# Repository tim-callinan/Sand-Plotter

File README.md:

# Sand-Plotter
This is my stab at building a Sand Plotter. Thank you to Jeff & co over the years. Sorry its taken me this long to upload my files. Ive included the mechanical Solidworks files, KiCAD ECAD files & Arduino code. I found it easier to design my own arduino shield with stepper drivers & arduino code. This machine has been working 8 hours a day, 7days a week probably for the last 4-5 months so I think its pretty reliable.

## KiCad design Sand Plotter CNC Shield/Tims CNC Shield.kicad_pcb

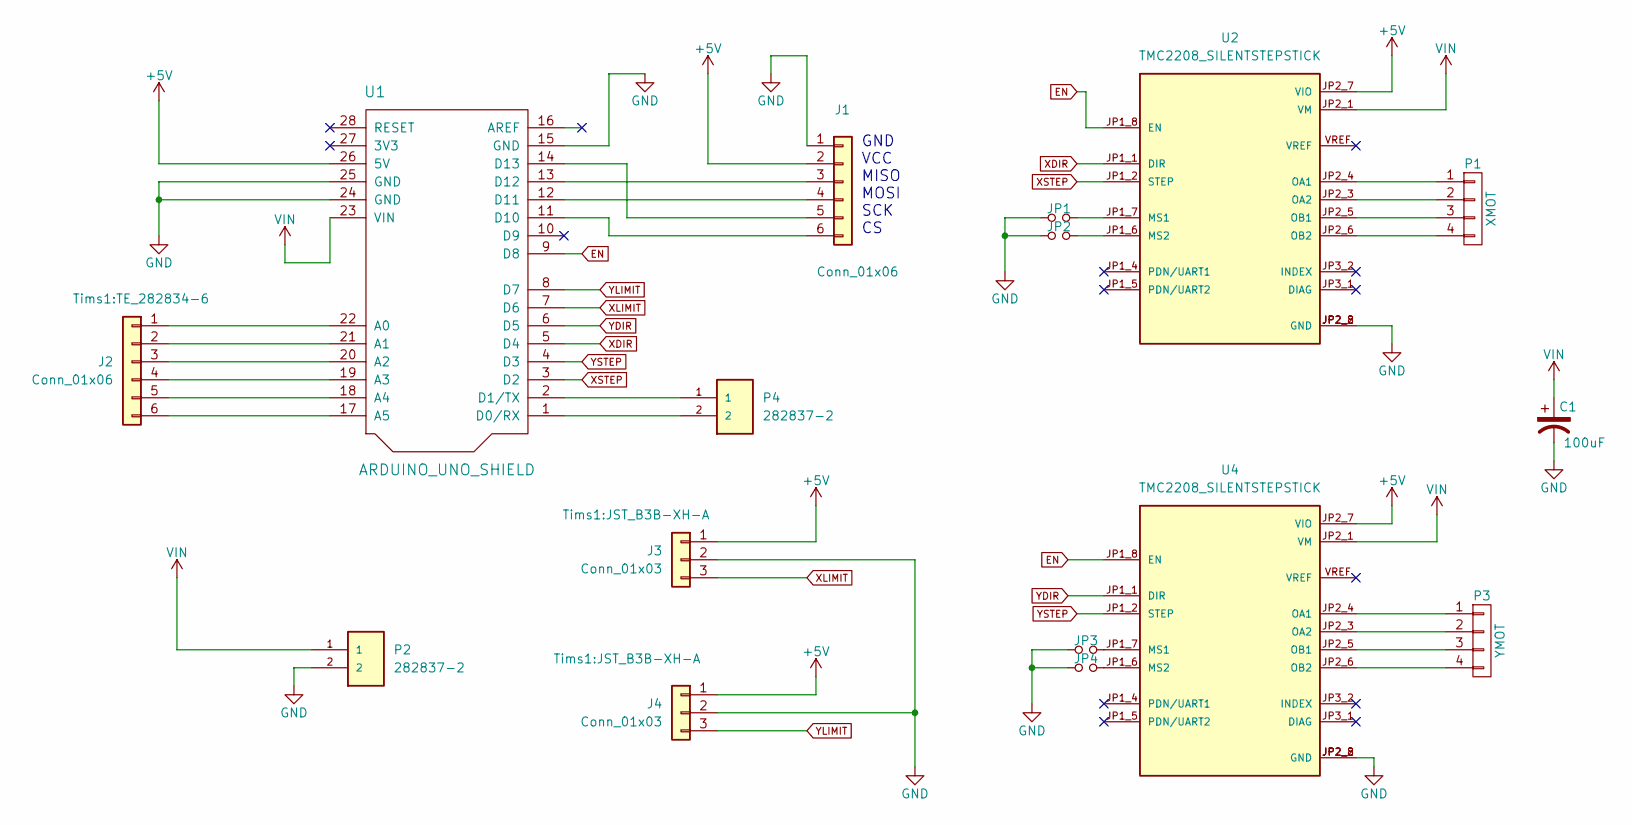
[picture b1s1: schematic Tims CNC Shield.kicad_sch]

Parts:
C1: 100uF; CP_Radial_D8.0mm_P3.50mm
J1: Conn_01x06; PinSocket_1x06_P2.54mm_Horizontal
J2: Conn_01x06; TE_282834-6
J3, J4: Conn_01x03; JST_B3B-XH-A
JP1, JP2, JP3, JP4: Jumper_NO_Small; PinHeader_1x02_P2.54mm_Vertical
P1: XMOT; PinHeader_1x04_P2.54mm_Vertical
P2, P4: 282837-2; TE_282837-2; PARTREV G3
P3: YMOT; PinHeader_1x04_P2.54mm_Vertical
U1: ARDUINO_UNO_SHIELD; ARDUINO_SHIELD
U2, U4: TMC2208_SILENTSTEPSTICK; MODULE_TMC2208_SILENTSTEPSTICK

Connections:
+5V: J1.2, J3.1, J4.1, U1.26 (5V), U2.JP2_7 (VIO), U4.JP2_7 (VIO)
EN: U1.9 (D8), U2.JP1_8 (EN), U4.JP1_8 (EN)
unnamed: J1.3, U1.13 (D12)
unnamed: J1.4, U1.12 (D11)
unnamed: J1.5, U1.14 (D13)
unnamed: J1.6, U1.11 (D10)
unnamed: J2.1, U1.22 (A0)
unnamed: J2.2, U1.21 (A1)
unnamed: J2.3, U1.20 (A2)
unnamed: J2.4, U1.19 (A3)
unnamed: J2.5, U1.18 (A4)
unnamed: P1.1, U2.JP2_4 (OA1)
unnamed: P1.2, U2.JP2_3 (OA2)
unnamed: P1.3, U2.JP2_5 (OB1)
unnamed: P1.4, U2.JP2_6 (OB2)
unnamed: P3.1, U4.JP2_4 (OA1)
unnamed: P3.2, U4.JP2_3 (OA2)
unnamed: P3.3, U4.JP2_5 (OB1)
unnamed: P3.4, U4.JP2_6 (OB2)
unnamed: P4.1, U1.2 (D1/TX)
unnamed: P4.2, U1.1 (D0/RX)
unnamed: JP1.2, U2.JP1_7 (MS1)
unnamed: JP2.2, U2.JP1_6 (MS2)
unnamed: JP3.2, U4.JP1_7 (MS1)
unnamed: JP4.2, U4.JP1_6 (MS2)
VIN: C1.1, P2.1, U1.23 (VIN), U2.JP2_1 (VM), U4.JP2_1 (VM)
XDIR: U1.5 (D4), U2.JP1_1 (DIR)
XLIMIT: J3.3, U1.7 (D6)
XSTEP: U1.3 (D2), U2.JP1_2 (STEP)
YDIR: U1.6 (D5), U4.JP1_1 (DIR)
YLIMIT: J4.3, U1.8 (D7)
YSTEP: U1.4 (D3), U4.JP1_2 (STEP)

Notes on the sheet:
GND VCC MISO MOSI SCK CS

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
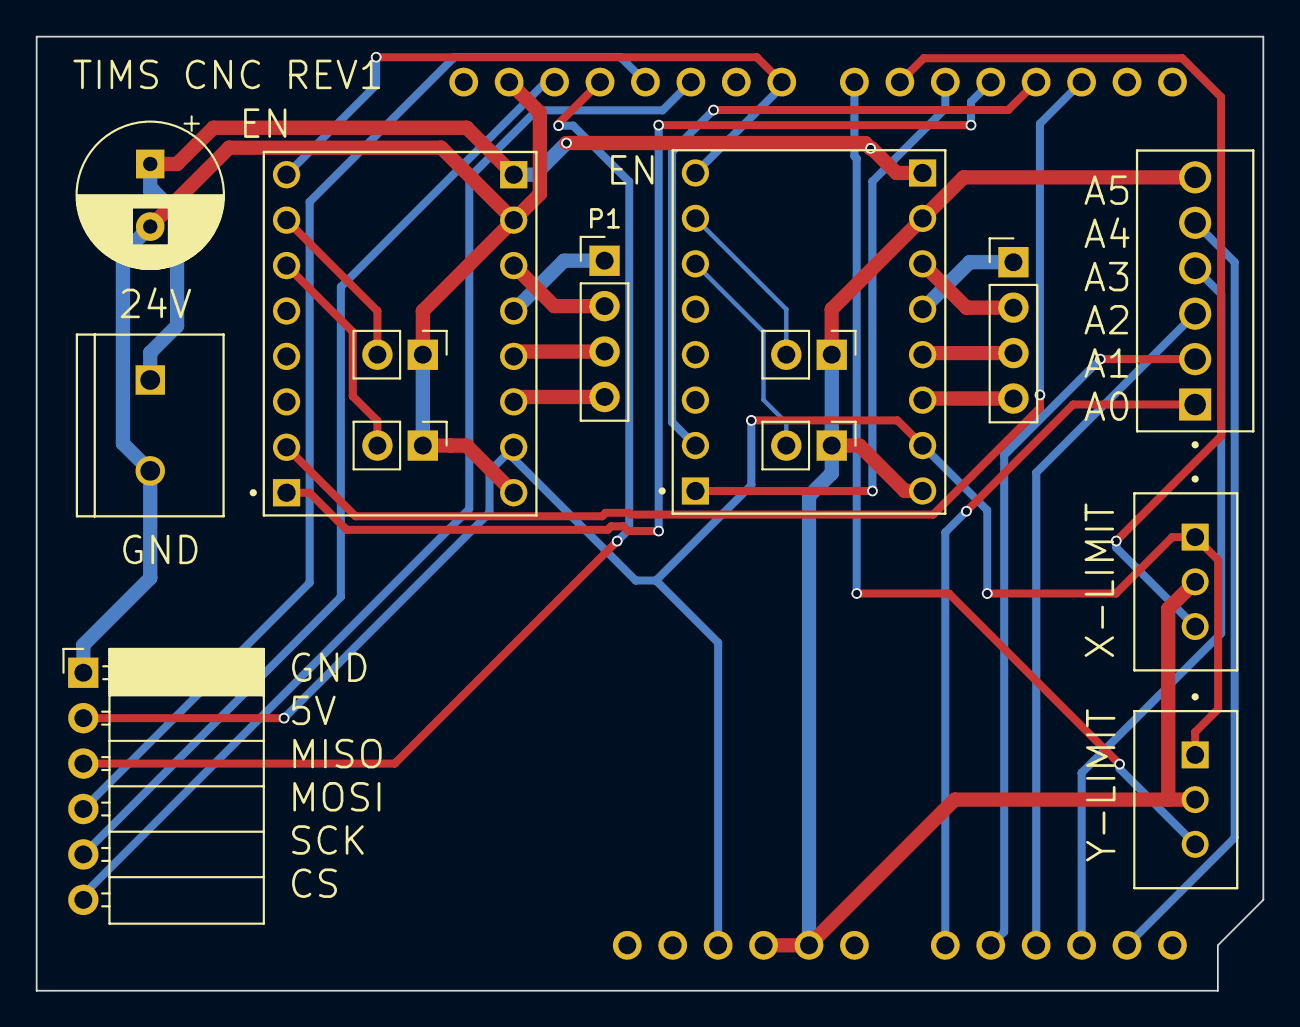
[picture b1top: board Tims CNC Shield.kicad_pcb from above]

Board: 2 copper layers, 68.6 x 53.3 mm, 15 parts (0 on the bottom side), 31 nets.
